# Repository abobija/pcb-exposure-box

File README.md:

# pcb-exposure-box
PCB Exposure Box made of an old Scanner

When you set the timer (max 999 seconds) with UP/DOWN buttons and then press button START, micro-controller-unit (MCU) PIC16F84A will turn on light and start to countdown to zero. When timer comes to zero, MCU will turn off the light signaling via the piezzo speaker that exposure process is done.

# Video presentation

Click [here](https://www.youtube.com/watch?v=MrX0DLpo7UE) to watch short video presentation on YouTube.

_Video was recorded back in 2013 and quality of video is very bad (sorry about that)._

# Development Environment

- MCU used for realization of this project is PIC16F84A and software for them was written in C using (and compiled with) [mikroC environment](https://www.mikroe.com/mikroc-pic)
- PCBs were designed using the [Eagle](https://www.autodesk.com/products/eagle/overview)

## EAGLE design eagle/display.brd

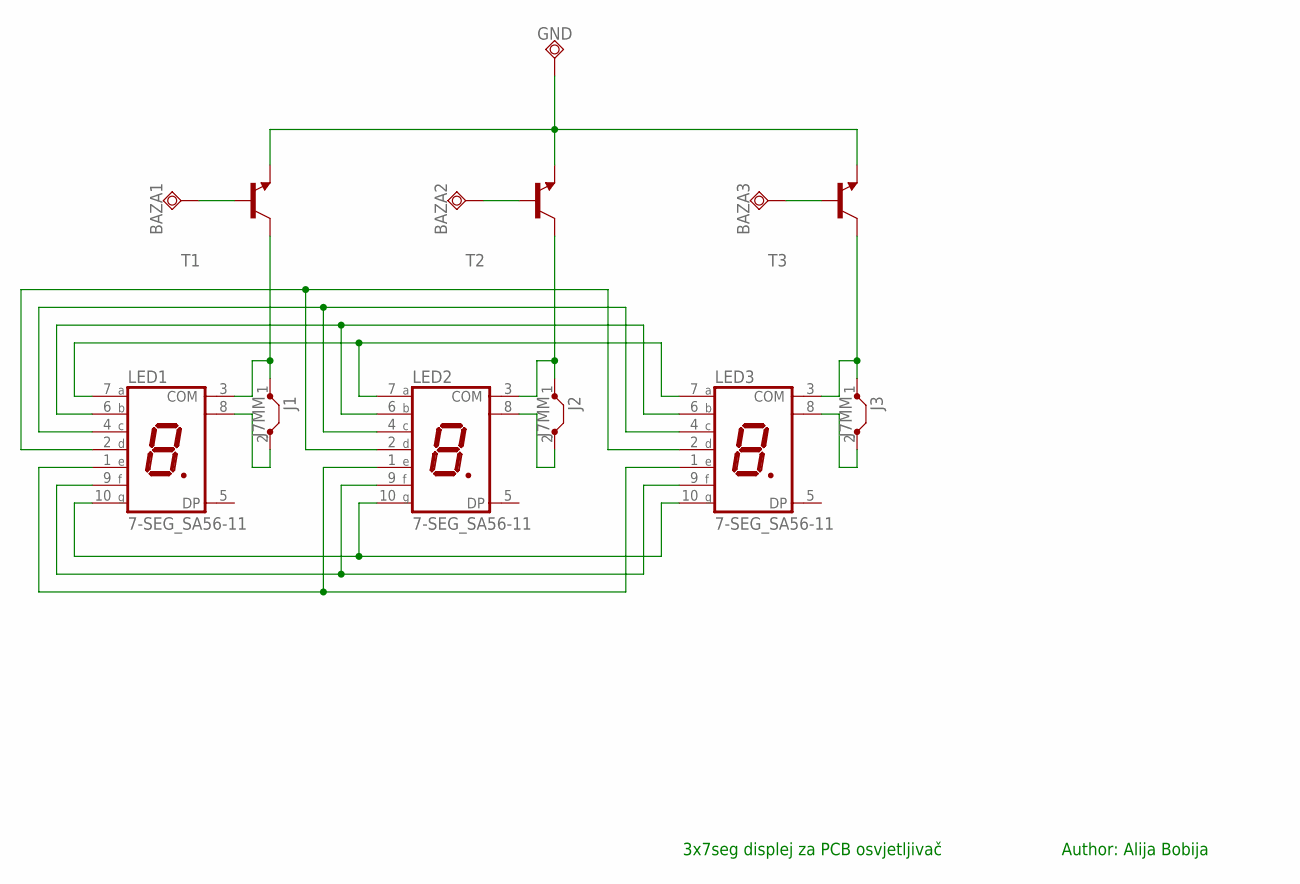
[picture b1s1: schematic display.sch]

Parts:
BAZA1, BAZA2, BAZA3: TPSQTP20SQ; TP20SQ
GND: TPSQTP20SQ; TP20SQ
J1, J2, J3: J7MM; 07
LED1, LED2, LED3: 7-SEG_SA56-11; SA56-11
T1, T2, T3: -NPN-SOT23-EBC; SOT23-EBC

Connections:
unnamed: LED1.7 (A), LED2.7 (A), LED3.7 (A)
unnamed: LED1.10 (G), LED2.10 (G), LED3.10 (G)
unnamed: LED1.6 (B), LED2.6 (B), LED3.6 (B)
unnamed: LED1.9 (F), LED2.9 (F), LED3.9 (F)
unnamed: LED1.4 (C), LED2.4 (C), LED3.4 (C)
unnamed: LED1.1 (E), LED2.1 (E), LED3.1 (E)
unnamed: LED1.2 (D), LED2.2 (D), LED3.2 (D)
unnamed: J1.1, LED1.3 (COM), T1.C
unnamed: J1.2, LED1.8 (COM)
unnamed: J2.1, LED2.3 (COM), T2.C
unnamed: J2.2, LED2.8 (COM)
unnamed: J3.1, LED3.3 (COM), T3.C
unnamed: J3.2, LED3.8 (COM)
unnamed: BAZA1.TP, T1.B
unnamed: BAZA2.TP, T2.B
unnamed: BAZA3.TP, T3.B
unnamed: GND.TP, T1.E, T2.E, T3.E

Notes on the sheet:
Author: Alija Bobija
3x7seg displej za PCB osvjetljivač

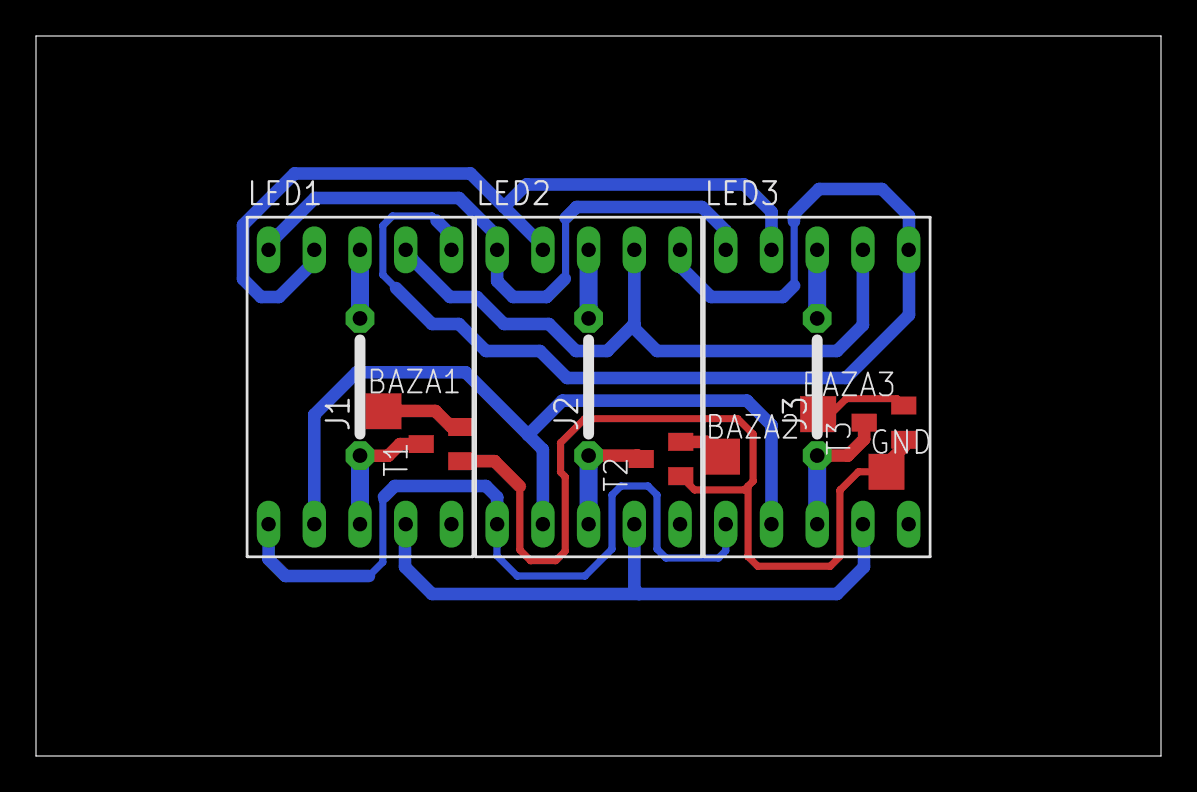
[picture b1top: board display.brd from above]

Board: 2 copper layers, 62.5 x 40.0 mm, 13 parts (0 on the bottom side), 17 nets.

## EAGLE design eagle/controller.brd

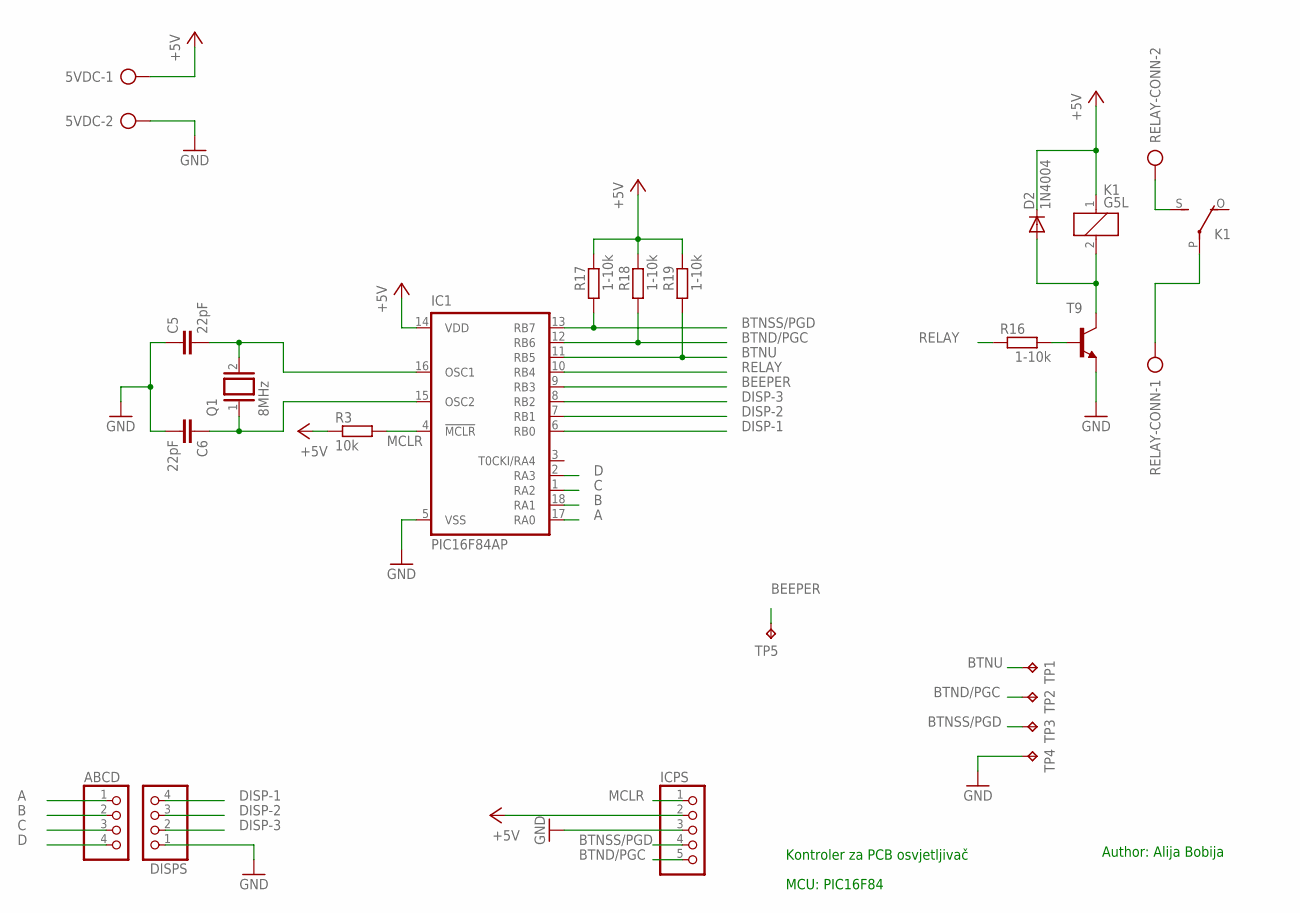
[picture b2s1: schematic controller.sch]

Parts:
5VDC: AK500/2
ABCD: PINHD-1X4; 1X04
C5, C6: 22pF; C025-024X044
D2: 1N4004; DO41-10
DISPS: PINHD-1X4; 1X04
IC1: PIC16F84AP; DIL18
ICPS: PINHD-1X5/90; 1X05/90
K1: G5L; G5LE
Q1: 8MHz; QS
R3: 10k; 0207/7
R16, R17, R18, R19: 1-10k; 0207/7
RELAY-CONN: AK500/2
T9: -NPN-SOT23-EBC; SOT23-EBC
TP1, TP2, TP3, TP4, TP5: TPTP15SQ; TP15SQ

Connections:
+5V: 5VDC.1, D2.C, IC1.14 (VDD), ICPS.2, K1.1, R3.1, R17.2, R18.2, R19.2
A: ABCD.1, IC1.17 (RA0)
B: ABCD.2, IC1.18 (RA1)
BEEPER: IC1.9 (RB3), TP5.TP
BTND/PGC: IC1.12 (RB6), ICPS.5, R18.1, TP2.TP
BTNSS/PGD: IC1.13 (RB7), ICPS.4, R17.1, TP3.TP
BTNU: IC1.11 (RB5), R19.1, TP1.TP
C: ABCD.3, IC1.1 (RA2)
D: ABCD.4, IC1.2 (RA3)
DISP-1: DISPS.4, IC1.6 (RB0)
DISP-2: DISPS.3, IC1.7 (RB1)
DISP-3: DISPS.2, IC1.8 (RB2)
GND: 5VDC.2, C5.1, C6.2, DISPS.1, IC1.5 (VSS), ICPS.3, T9.E, TP4.TP
MCLR: IC1.4 (!MCLR), ICPS.1, R3.2
unnamed: C5.2, IC1.16 (OSC1), Q1.2
unnamed: C6.1, IC1.15 (OSC2), Q1.1
unnamed: K1.S, RELAY-CONN.2
unnamed: D2.A, K1.2, T9.C
unnamed: R16.2, T9.B
unnamed: K1.P, RELAY-CONN.1
RELAY: IC1.10 (RB4), R16.1

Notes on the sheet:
Kontroler za PCB osvjetljivač
MCU: PIC16F84
Author: Alija Bobija

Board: 2 copper layers, 22 parts (0 on the bottom side), 21 nets, no tracks yet.

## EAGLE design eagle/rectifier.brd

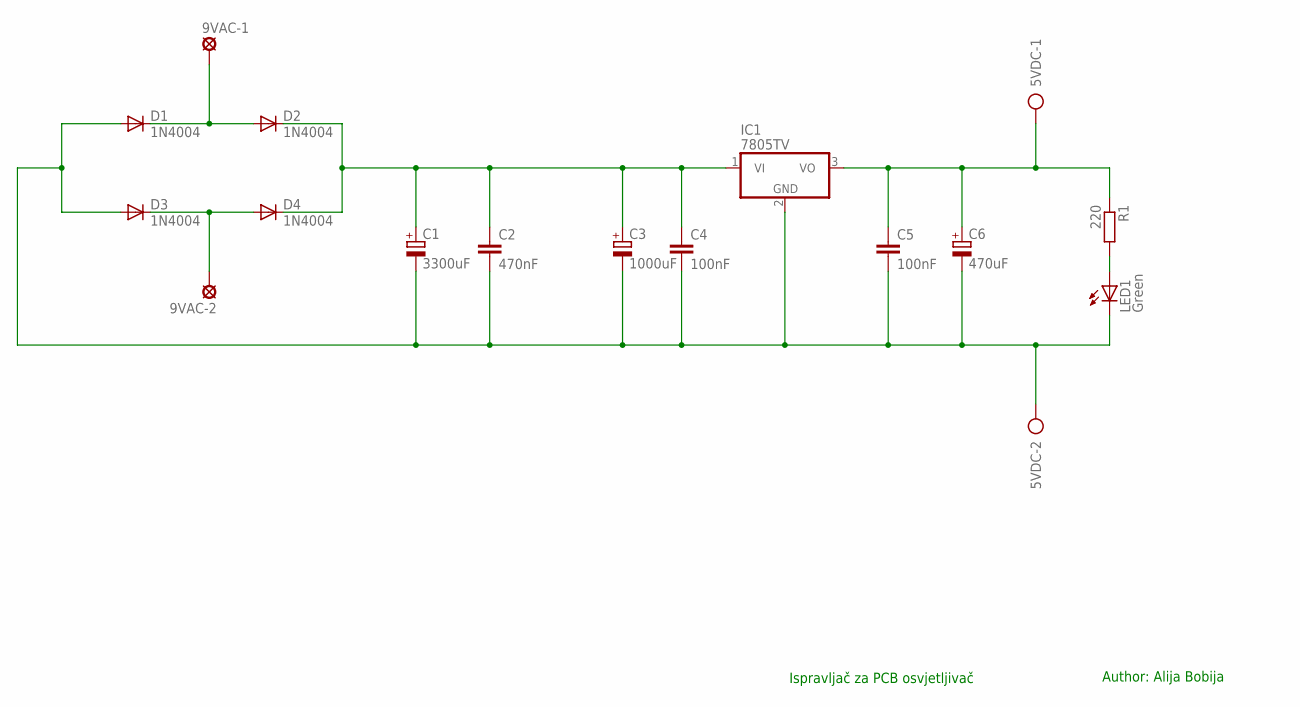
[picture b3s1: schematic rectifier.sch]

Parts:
5VDC: AK500/2
9VAC-1, 9VAC-2: LSP10
C1: 3300uF; E5-13
C2: 470nF; C050-024X044
C3: 1000uF; E3,5-10
C4, C5: 100nF; C025-024X044
C6: 470uF; E3,5-8
D1, D2, D3, D4: 1N4004; DO41-10
IC1: 7805TV; TO220V
LED1: Green; LED3MM
R1: 220; M0805

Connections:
GND: 5VDC.2, C1.-, C2.2, C3.-, C4.2, C5.2, C6.-, D1.A, D3.A, IC1.2 (GND), LED1.K (C)
unnamed: 9VAC-1.MP, D1.C, D2.A
unnamed: 9VAC-2.MP, D3.C, D4.A
unnamed: C1.+, C2.1, C3.+, C4.1, D2.C, D4.C, IC1.1 (VI)
unnamed: 5VDC.1, C5.1, C6.+, IC1.3 (VO), R1.1
unnamed: LED1.A, R1.2

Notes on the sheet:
Author: Alija Bobija
Ispravljač za PCB osvjetljivač

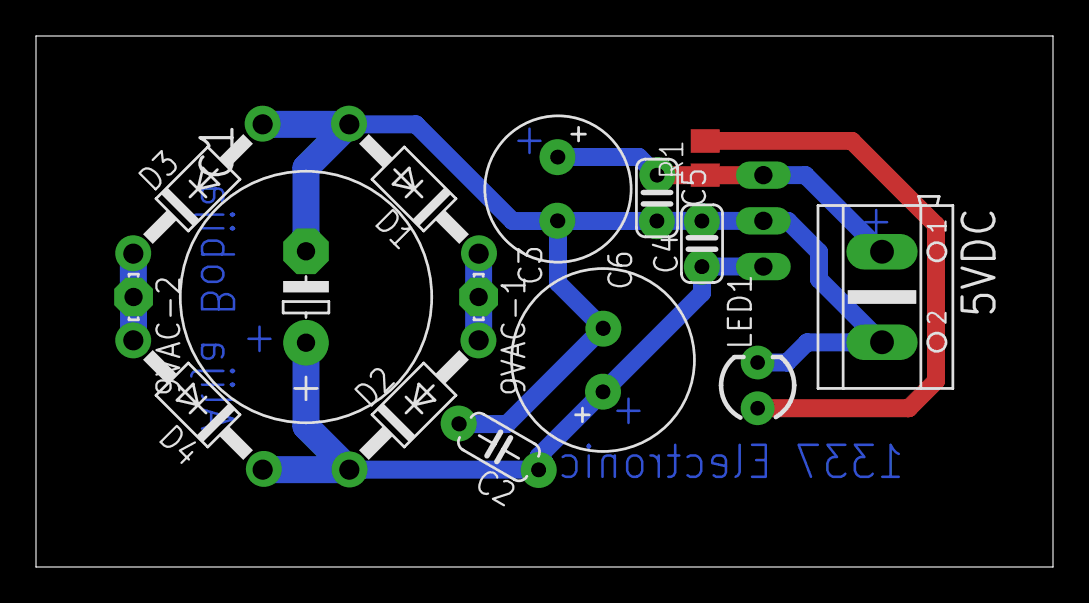
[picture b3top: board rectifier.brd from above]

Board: 2 copper layers, 56.5 x 29.5 mm, 16 parts (1 on the bottom side), 6 nets.

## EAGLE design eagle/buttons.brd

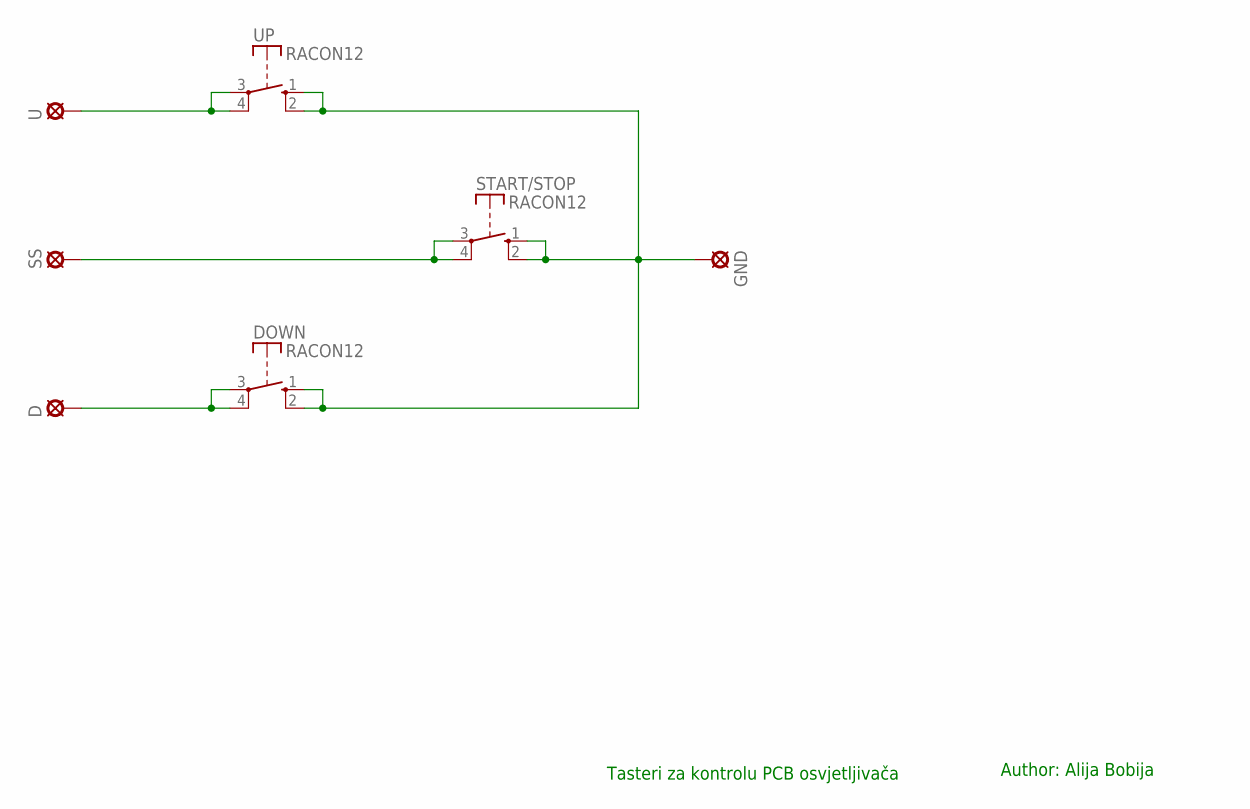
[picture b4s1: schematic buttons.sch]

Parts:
D: SE11
DOWN: RACON12
GND: SE11
SS: SE11
START/STOP: RACON12
U: SE11
UP: RACON12

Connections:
unnamed: DOWN.1 (S), DOWN.2 (S), GND.MP, START/STOP.1 (S), START/STOP.2 (S), UP.1 (S), UP.2 (S)
unnamed: U.MP, UP.3, UP.4
unnamed: D.MP, DOWN.3, DOWN.4
unnamed: SS.MP, START/STOP.3, START/STOP.4

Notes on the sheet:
Author: Alija Bobija
Tasteri za kontrolu PCB osvjetljivača

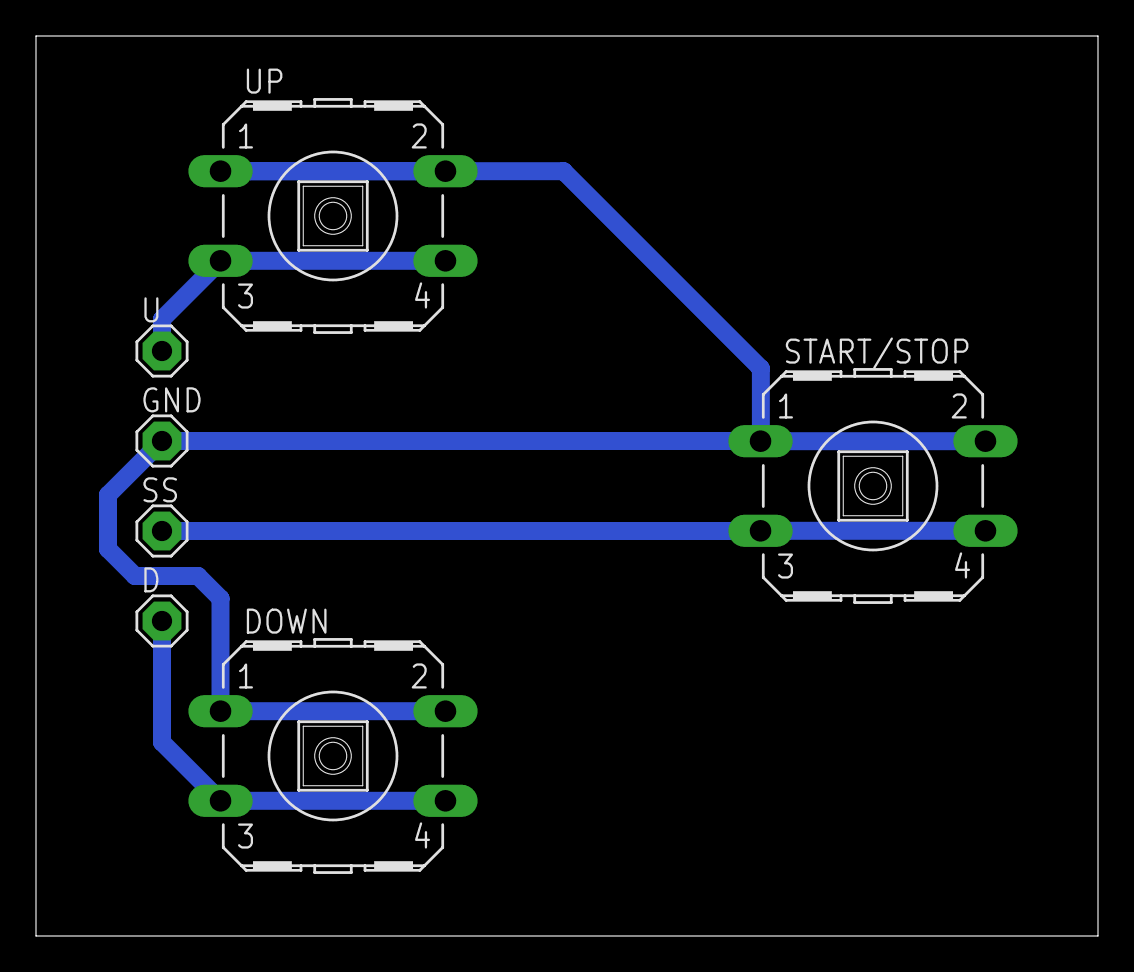
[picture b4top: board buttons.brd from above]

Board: 2 copper layers, 59.0 x 50.0 mm, 7 parts (0 on the bottom side), 4 nets.

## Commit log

2019-03-20 Update README
    Fixed link for mikroC
2019-03-20 Typo fixes

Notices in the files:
parts and their libraries:
sparkfun-LED: Licensing: Creative Commons ShareAlike 4.0 International - https://creativecommons.org/licenses/by-sa/4.0
